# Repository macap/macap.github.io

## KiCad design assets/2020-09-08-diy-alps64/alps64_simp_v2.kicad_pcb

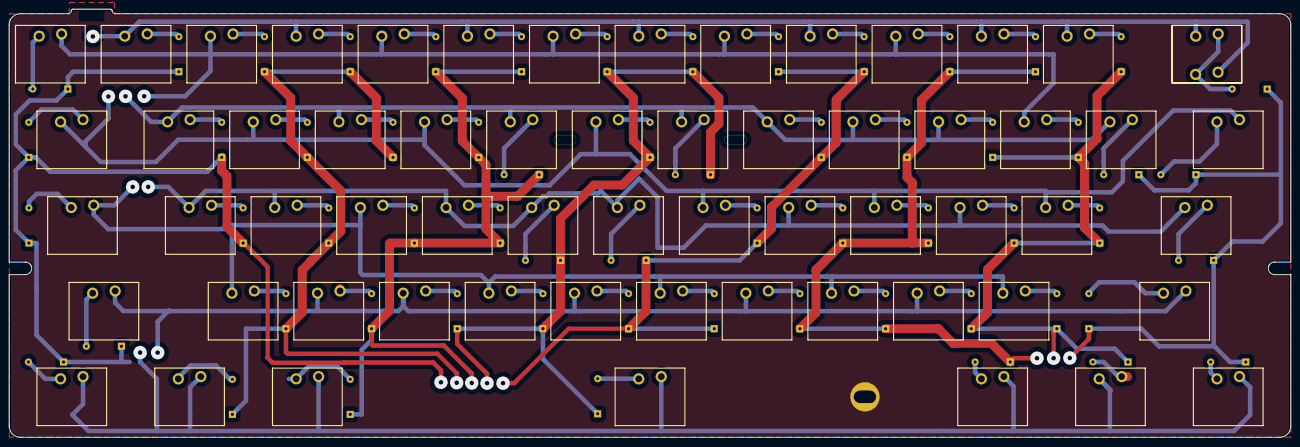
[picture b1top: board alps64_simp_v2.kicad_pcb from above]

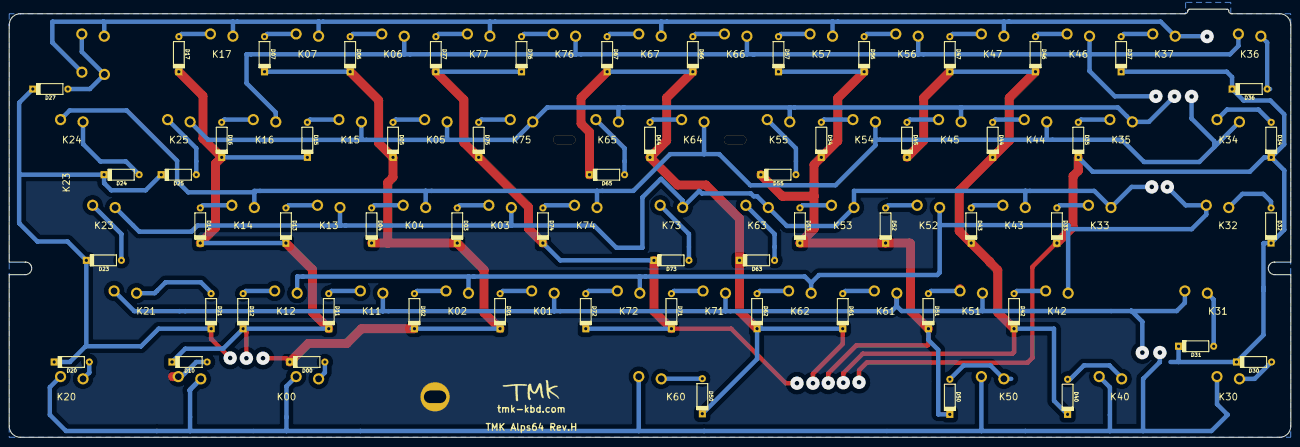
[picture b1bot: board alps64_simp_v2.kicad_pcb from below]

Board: 2 copper layers, 285.0 x 95.2 mm, 126 parts (60 on the bottom side), 76 nets.

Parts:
D00, D01, D02, D03, D04, D05, D06, D07, D10, D11, D12, D13, D14, D15, D16, D17, D20, D21, D23, D24, D25, D27, D30, D31, D32, D33, D34, D35, D36, D37, D40, D42, D43, D44, D45, D46, D47, D50, D50#2, D51, D52, D53, D54, D55, D56, D57, D61, D62, D63, D64, D65, D66, D67, D71, D72, D73, D74, D75, D76, D77: D; diode_without_smd
K00, K20, K21, K24, K30, K31, K32, K36, K40, K50, K60: KEYSW; ALPS_SKCM_reverse_pad
K01, K02, K03, K04, K05, K06, K07, K10_2, K11, K12, K13, K14, K15, K16, K17, K23, K25, K27_1, K27_1#2, K33, K34, K35, K37, K42, K43, K44, K45, K46, K47, K51, K52, K53, K54, K55, K56, K57, K61, K62, K63, K64, K65, K66, K67, K71, K72, K73, K74, K75, K76, K77: KEYSW; ALPS_SKCM
Poker_oval_hole: VAL**; Poker_oval_hole
Poker_oval_hole#2, Poker_oval_hole#3: VAL**; Poker_oval_hole
Poker_side_edge_long: VAL**; Poker_side_edge_long
Poker_side_edge_long#2: VAL**; Poker_side_edge_long

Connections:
/matrix/col0: K00.1, K10_2.1, K20.1, K30.1, K40.1, K50.1, K60.1
/matrix/col1: K01.1, K11.1, K21.1, K31.1, K51.1, K61.1, K71.1
/matrix/col2: K02.1, K12.1, K32.1, K42.1, K52.1, K62.1, K72.1
/matrix/col3: K03.1, K13.1, K23.1, K33.1, K43.1, K53.1, K63.1, K73.1
/matrix/col4: K04.1, K14.1, K24.1, K34.1, K44.1, K54.1, K64.1, K74.1
/matrix/col5: K05.1, K15.1, K25.1, K35.1, K45.1, K55.1, K65.1, K75.1
/matrix/col6: K06.1, K16.1, K36.1, K46.1, K56.1, K66.1, K76.1
/matrix/col7: K07.1, K17.1, K27_1.1, K27_1#2.1, K37.1, K47.1, K57.1, K67.1, K77.1
/matrix/row0: D00.2, D01.2, D02.2, D03.2, D04.2, D05.2, D06.2, D07.2
/matrix/row1: D10.2, D11.2, D12.2, D13.2, D14.2, D15.2, D16.2, D17.2
/matrix/row2: D20.2, D21.2, D23.2, D24.2, D25.2, D27.2
/matrix/row3: D30.2, D31.2, D32.2, D33.2, D34.2, D35.2, D36.2, D37.2
/matrix/row4: D40.2, D42.2, D43.2, D44.2, D45.2, D46.2, D47.2
/matrix/row5: D50#2.2, D51.2, D52.2, D53.2, D54.2, D55.2, D56.2, D57.2
/matrix/row6: D50.2, D61.2, D62.2, D63.2, D64.2, D65.2, D66.2, D67.2
/matrix/row7: D71.2, D72.2, D73.2, D74.2, D75.2, D76.2, D77.2
unnamed: D00.1, K00.2
unnamed: D01.1, K01.2
unnamed: D02.1, K02.2
unnamed: D03.1, K03.2
unnamed: D04.1, K04.2
unnamed: D05.1, K05.2
unnamed: D06.1, K06.2
unnamed: D07.1, K07.2
unnamed: D10.1, K10_2.2
unnamed: D11.1, K11.2
unnamed: D12.1, K12.2
unnamed: D13.1, K13.2
unnamed: D14.1, K14.2
unnamed: D15.1, K15.2
unnamed: D16.1, K16.2
unnamed: D17.1, K17.2
unnamed: D20.1, K20.2
unnamed: D21.1, K21.2
unnamed: D23.1, K23.2
unnamed: D24.1, K24.2
unnamed: D25.1, K25.2
unnamed: D27.1, K27_1.2, K27_1#2.2
unnamed: D30.1, K30.2
unnamed: D31.1, K31.2
unnamed: D32.1, K32.2
unnamed: D33.1, K33.2
unnamed: D34.1, K34.2
unnamed: D35.1, K35.2
unnamed: D36.1, K36.2
unnamed: D37.1, K37.2
unnamed: D40.1, K40.2
unnamed: D42.1, K42.2
unnamed: D43.1, K43.2
unnamed: D44.1, K44.2
unnamed: D45.1, K45.2
unnamed: D46.1, K46.2
unnamed: D47.1, K47.2
unnamed: D50#2.1, K50.2
unnamed: D51.1, K51.2
unnamed: D52.1, K52.2
unnamed: D53.1, K53.2
unnamed: D54.1, K54.2
unnamed: D55.1, K55.2
unnamed: D56.1, K56.2
unnamed: D57.1, K57.2
unnamed: D50.1, K60.2
unnamed: D61.1, K61.2
unnamed: D62.1, K62.2
unnamed: D63.1, K63.2
unnamed: D64.1, K64.2
unnamed: D65.1, K65.2
unnamed: D66.1, K66.2
unnamed: D67.1, K67.2
unnamed: D71.1, K71.2
unnamed: D72.1, K72.2
unnamed: D73.1, K73.2
unnamed: D74.1, K74.2
unnamed: D75.1, K75.2
unnamed: D76.1, K76.2
unnamed: D77.1, K77.2

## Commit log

2020-08-01 Jekyll initial commit
2020-08-01 Config update
2020-08-01 Update gemfile for github pages
2020-08-01 Cleanup
2020-08-01 Post: Diy sony remote arduino
2020-08-01 Removes empty about page
2020-09-08 DIY 60% AEK/alps64 mechanical keyboard
2020-09-08 Fix main image in alps64 article
2020-09-08 Adds visits counter
2020-09-08 Adds current post url to view counter
2020-09-10 Adds pics to sony post
2020-09-10 Fix kicad file link
2020-09-12 Update cover photo and add pcb
2020-09-27 Adds AWS frontend repost
2021-05-20 Bump nokogiri from 1.10.10 to 1.11.5
    Bumps [nokogiri](https://github.com/sparklemotion/nokogiri) from 1.10.10 to 1.11.5.
    - [Release notes](https://github.com/sparklemotion/nokogiri/releases)
    - [Changelog](https://github.com/sparklemotion/nokogiri/blob/main/CHANGELOG.md)
    - [Commits](https://github.com/sparklemotion/nokogiri/compare/v1.10.10...v1.11.5)
2021-07-13 Bump addressable from 2.7.0 to 2.8.0
    Bumps [addressable](https://github.com/sporkmonger/addressable) from 2.7.0 to 2.8.0.
    - [Release notes](https://github.com/sporkmonger/addressable/releases)
    - [Changelog](https://github.com/sporkmonger/addressable/blob/main/CHANGELOG.md)
    - [Commits](https://github.com/sporkmonger/addressable/compare/addressable-2.7.0...addressable-2.8.0)
    ---
    updated-dependencies:
2021-09-28 Bump nokogiri from 1.10.10 to 1.12.5
    Bumps [nokogiri](https://github.com/sparklemotion/nokogiri) from 1.10.10 to 1.12.5.
    - [Release notes](https://github.com/sparklemotion/nokogiri/releases)
    - [Changelog](https://github.com/sparklemotion/nokogiri/blob/main/CHANGELOG.md)
    - [Commits](https://github.com/sparklemotion/nokogiri/compare/v1.10.10...v1.12.5)
    ---
    updated-dependencies:
2021-09-29 Adds "Working jailbreak for iOS 8.4.1 in 2021"
2021-09-29 Adds "Controlling iOS device programmatically"
2022-02-26 Bump nokogiri from 1.10.10 to 1.13.3
    Bumps [nokogiri](https://github.com/sparklemotion/nokogiri) from 1.10.10 to 1.13.3.
    - [Release notes](https://github.com/sparklemotion/nokogiri/releases)
    - [Changelog](https://github.com/sparklemotion/nokogiri/blob/main/CHANGELOG.md)
    - [Commits](https://github.com/sparklemotion/nokogiri/compare/v1.10.10...v1.13.3)
    ---
    updated-dependencies:
2022-04-12 Bump nokogiri from 1.10.10 to 1.13.4
    Bumps [nokogiri](https://github.com/sparklemotion/nokogiri) from 1.10.10 to 1.13.4.
    - [Release notes](https://github.com/sparklemotion/nokogiri/releases)
    - [Changelog](https://github.com/sparklemotion/nokogiri/blob/v1.13.4/CHANGELOG.md)
    - [Commits](https://github.com/sparklemotion/nokogiri/compare/v1.10.10...v1.13.4)
    ---
    updated-dependencies:
2022-05-19 Bump nokogiri from 1.10.10 to 1.13.6
    Bumps [nokogiri](https://github.com/sparklemotion/nokogiri) from 1.10.10 to 1.13.6.
    - [Release notes](https://github.com/sparklemotion/nokogiri/releases)
    - [Changelog](https://github.com/sparklemotion/nokogiri/blob/main/CHANGELOG.md)
    - [Commits](https://github.com/sparklemotion/nokogiri/compare/v1.10.10...v1.13.6)
    ---
    updated-dependencies:
2022-06-07 Adds umami analytics
2022-06-26 Adds google site verification
2022-07-22 Bump tzinfo from 1.2.7 to 1.2.10
    Bumps [tzinfo](https://github.com/tzinfo/tzinfo) from 1.2.7 to 1.2.10.
    - [Release notes](https://github.com/tzinfo/tzinfo/releases)
    - [Changelog](https://github.com/tzinfo/tzinfo/blob/master/CHANGES.md)
    - [Commits](https://github.com/tzinfo/tzinfo/compare/v1.2.7...v1.2.10)
    ---
    updated-dependencies:
2022-10-06 Bump addressable from 2.7.0 to 2.8.1
    Bumps [addressable](https://github.com/sporkmonger/addressable) from 2.7.0 to 2.8.1.
    - [Release notes](https://github.com/sporkmonger/addressable/releases)
    - [Changelog](https://github.com/sporkmonger/addressable/blob/main/CHANGELOG.md)
    - [Commits](https://github.com/sporkmonger/addressable/compare/addressable-2.7.0...addressable-2.8.1)
    ---
    updated-dependencies:
2022-10-20 Bump nokogiri from 1.10.10 to 1.13.9
    Bumps [nokogiri](https://github.com/sparklemotion/nokogiri) from 1.10.10 to 1.13.9.
    - [Release notes](https://github.com/sparklemotion/nokogiri/releases)
    - [Changelog](https://github.com/sparklemotion/nokogiri/blob/main/CHANGELOG.md)
    - [Commits](https://github.com/sparklemotion/nokogiri/compare/v1.10.10...v1.13.9)
    ---
    updated-dependencies:
2023-02-01 Bump activesupport from 5.2.4.3 to 6.0.6.1
    Bumps [activesupport](https://github.com/rails/rails) from 5.2.4.3 to 6.0.6.1.
    - [Release notes](https://github.com/rails/rails/releases)
    - [Changelog](https://github.com/rails/rails/blob/v7.0.4.2/activesupport/CHANGELOG.md)
    - [Commits](https://github.com/rails/rails/compare/v5.2.4.3...v6.0.6.1)
    ---
    updated-dependencies:
2023-04-11 Bump nokogiri from 1.10.10 to 1.14.3
    Bumps [nokogiri](https://github.com/sparklemotion/nokogiri) from 1.10.10 to 1.14.3.
    - [Release notes](https://github.com/sparklemotion/nokogiri/releases)
    - [Changelog](https://github.com/sparklemotion/nokogiri/blob/main/CHANGELOG.md)
    - [Commits](https://github.com/sparklemotion/nokogiri/compare/v1.10.10...v1.14.3)
    ---
    updated-dependencies:
2024-05-22 Adds "Allow non-root user to run command as root without password"
2025-02-09 Adds bash-commander post; updates gitignore
2025-02-09 fix bash commander screenshot
2025-02-09 update umami code
2025-04-11 Adds anti spam ios shortcut post
2025-04-11 fix pub date
